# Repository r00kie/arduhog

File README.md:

# Arduhog #

The aim of this project is to create pcb diagrams and software thanks to it will be possible to build hardware cockpit simulator for DCS A10C (and maybe more). PCB board and software try to simulate HID interface (keyboard exactly), so the knowledge that it is available here should also fit for other simulators/games. 

I'm lazy so im using Arduino Nano as main controller, it's cheap (if you are using chinese replacements), it's popular, you don't need any advanced hardware programmer and when you will be bored with this project you can use it for something else.

Project requires [this library](https://git.io/vgGM2) for working. You have to install it in your Arduino IDE.

You can also check [DCS-Bios](http://dcs-bios.a10c.de/), but it have a different approach, it's requires installing some additional scripts in DCS World and it's works only with A10C Cocpit. 

## Project Structure Description

### Hardware ###

  * eagle/ - directory containing EAGLE project; 
  * eagle/main_board - pcb diagrams for main board; mainly it contains all necessary components to simulate hardware keyboard and other stuff to indicate device status, some buttons (currently they do nothing); main board have 8 expansions port for extension board, it allows you to, theoretically, support up to 64 buttons/switches; connection to the PC is done via the USB B port (why B? because it is the simplest USB port for soldering and it fit to 100 mil boards)
  * eagle/ext_board - pcb diagrams for extension board; thanks to this board you can connect up to 16 button; 
  * eagle/ahcp - only schematic, how to connect switches from Armament Hud Control Panel to port what will fit extension board;
  * eagle/bom/* - Bill of Materials for pcb boards;
  * eagle/tests/* - tests and early material created for this project;

### Software ###

  * src/arduhog/* - source code for arduino controller;
  * src/arduhog/keymappings.ods - spreedsheet containing mapping from eagle/ahcp.sch to buttons in code and shortcuts in game.  

## Screenshots, images and movies  
  
  * [Image gallery of prototype](https://imgur.com/a/71ZCE)
  * [Working prototype](https://vid.me/YhLZ)

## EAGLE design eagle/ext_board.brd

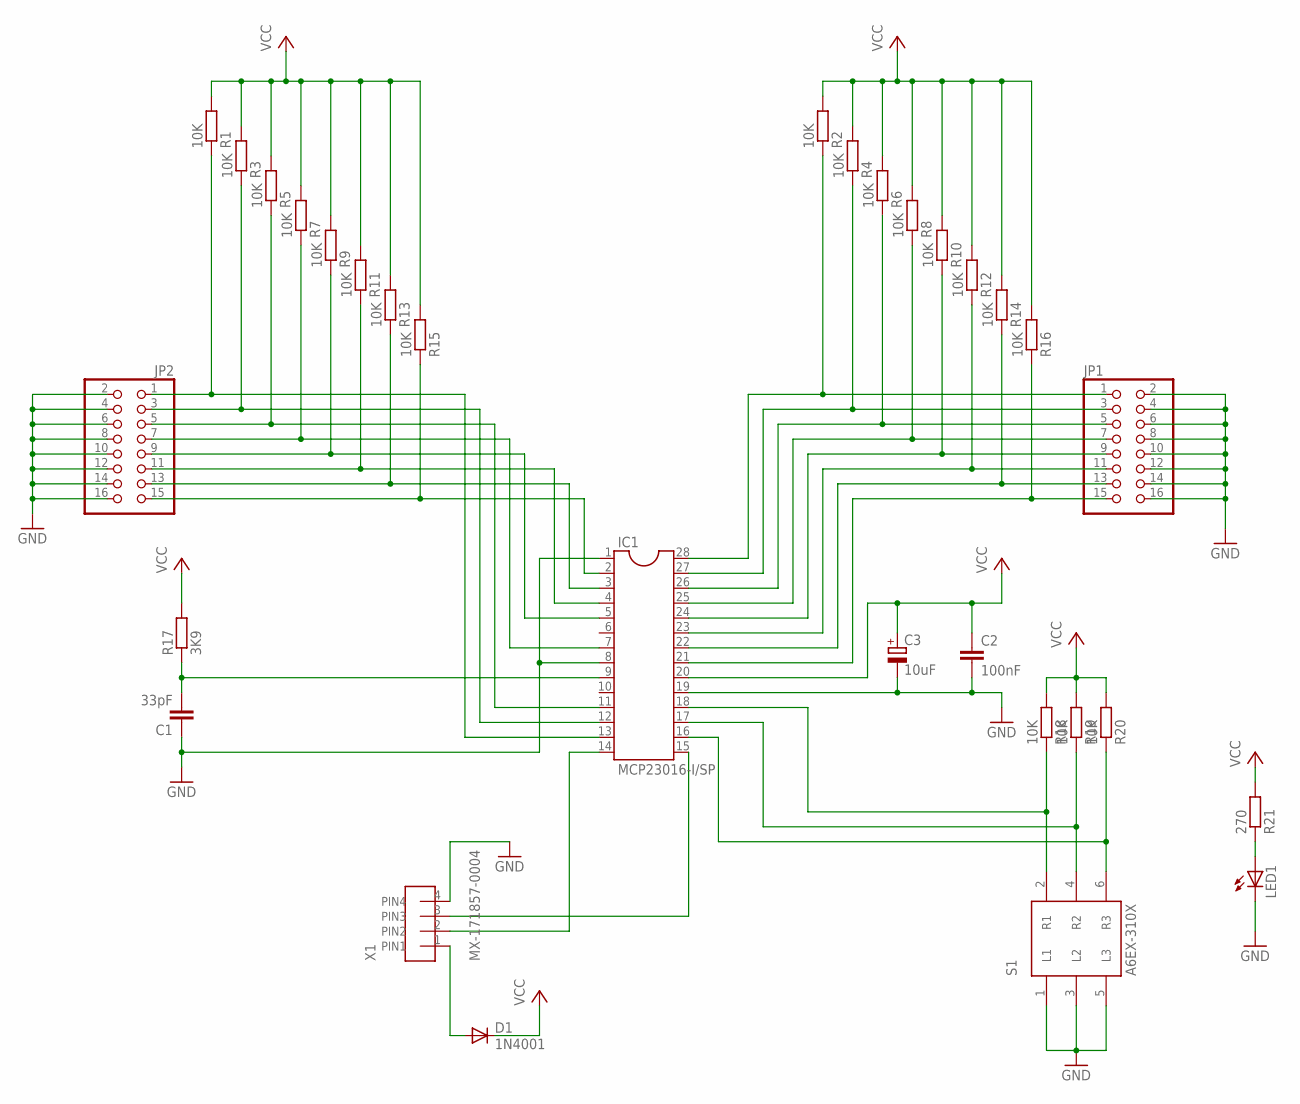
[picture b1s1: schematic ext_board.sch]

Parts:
C1: 33pF; C050-030X075
C2: 100nF; C050-030X075
C3: 10uF; E2,5-7
D1: 1N4001; DO41-10
IC1: MCP23016-I/SP; DIL28-3
JP1, JP2: PINHD-2X8; 2X08
LED1: LED3MM
R1, R2, R3, R4, R5, R6, R7, R8, R9, R10, R11, R12, R13, R14, R15, R16, R18, R19, R20: 10K; 0204/7
R17: 3K9; 0204/7
R21: 270; 0204/7
S1: A6EX-310X
X1: MX-171857-0004

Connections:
GND: C1.1, C2.2, C3.-, IC1.1, IC1.8, IC1.19, JP1.2, JP1.4, JP1.6, JP1.8, JP1.10, JP1.12, JP1.14, JP1.16, JP2.2, JP2.4, JP2.6, JP2.8, JP2.10, JP2.12, JP2.14, JP2.16, LED1.K (C), S1.1 (L1), S1.3 (L2), S1.5 (L3), X1.4 (PIN4)
GP0.0: IC1.21, JP1.15, R16.1
GP0.1: IC1.22, JP1.13, R14.1
GP0.2: IC1.23, JP1.11, R12.1
GP0.3: IC1.2, JP2.15, R15.1
GP0.4: IC1.3, JP2.13, R13.1
GP0.5: IC1.4, JP2.11, R11.1
unnamed: C1.2, IC1.9, R17.1
unnamed: IC1.18, R18.1, S1.2 (R1)
unnamed: IC1.17, R19.1, S1.4 (R2)
unnamed: IC1.5, JP2.9, R9.1
unnamed: IC1.7, JP2.7, R7.1
unnamed: D1.A, X1.1 (PIN1)
unnamed: IC1.11, JP2.5, R5.1
unnamed: IC1.16, R20.1, S1.6 (R3)
unnamed: IC1.24, JP1.9, R10.1
unnamed: IC1.25, JP1.7, R8.1
unnamed: IC1.26, JP1.5, R6.1
unnamed: IC1.27, JP1.3, R4.1
unnamed: IC1.28, JP1.1, R2.1
unnamed: IC1.12, JP2.3, R3.1
unnamed: IC1.13, JP2.1, R1.1
unnamed: LED1.A, R21.1
SCL: IC1.14, X1.2 (PIN2)
SDA: IC1.15, X1.3 (PIN3)
VCC: C2.1, C3.+, D1.C, IC1.20, R1.2, R2.2, R3.2, R4.2, R5.2, R6.2, R7.2, R8.2, R9.2, R10.2, R11.2, R12.2, R13.2, R14.2, R15.2, R16.2, R17.2, R18.2, R19.2, R20.2, R21.2

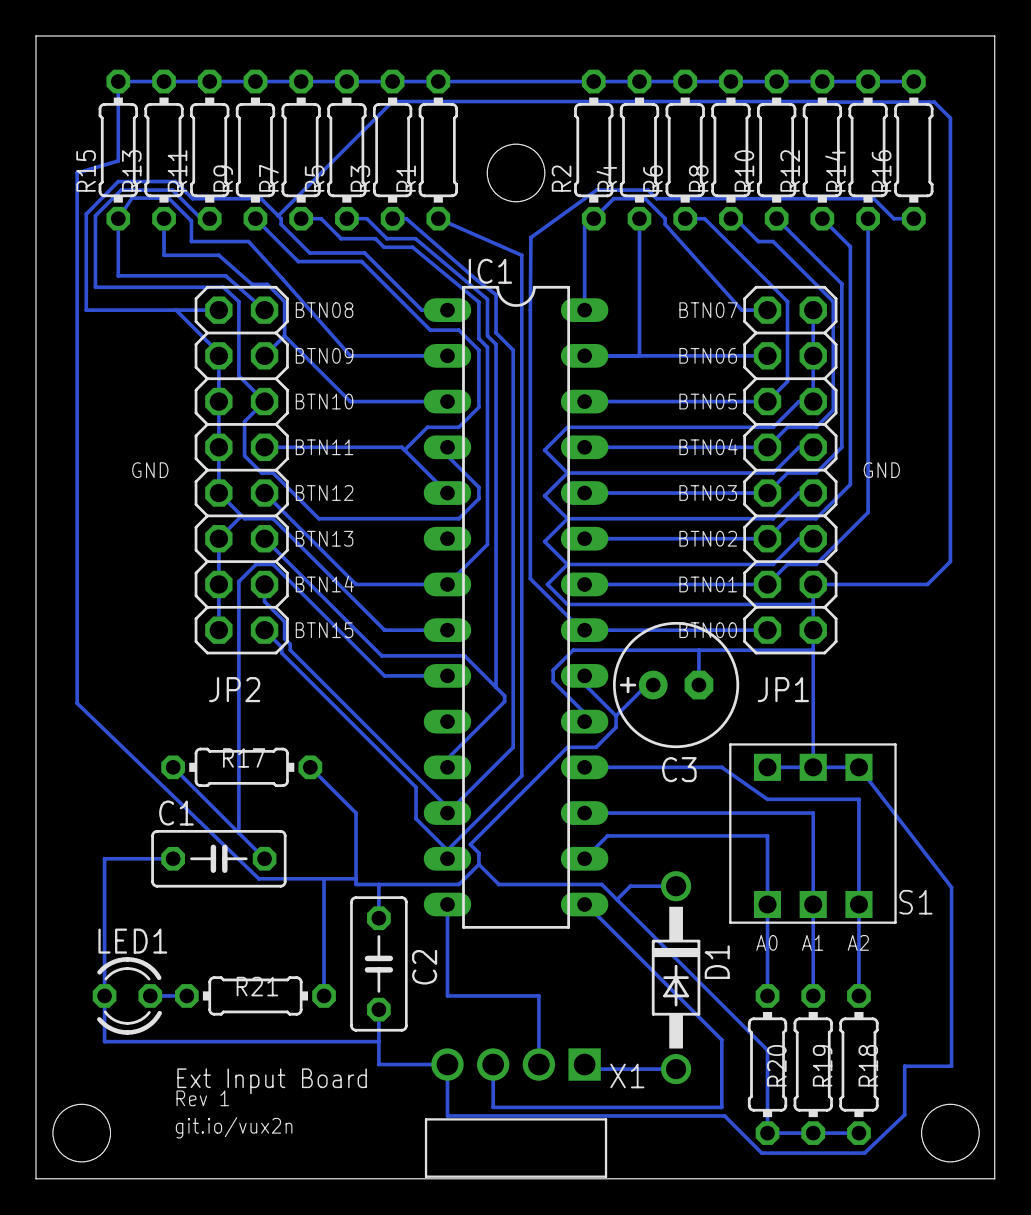
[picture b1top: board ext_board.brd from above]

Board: 2 copper layers, 53.3 x 63.5 mm, 31 parts (0 on the bottom side), 26 nets.

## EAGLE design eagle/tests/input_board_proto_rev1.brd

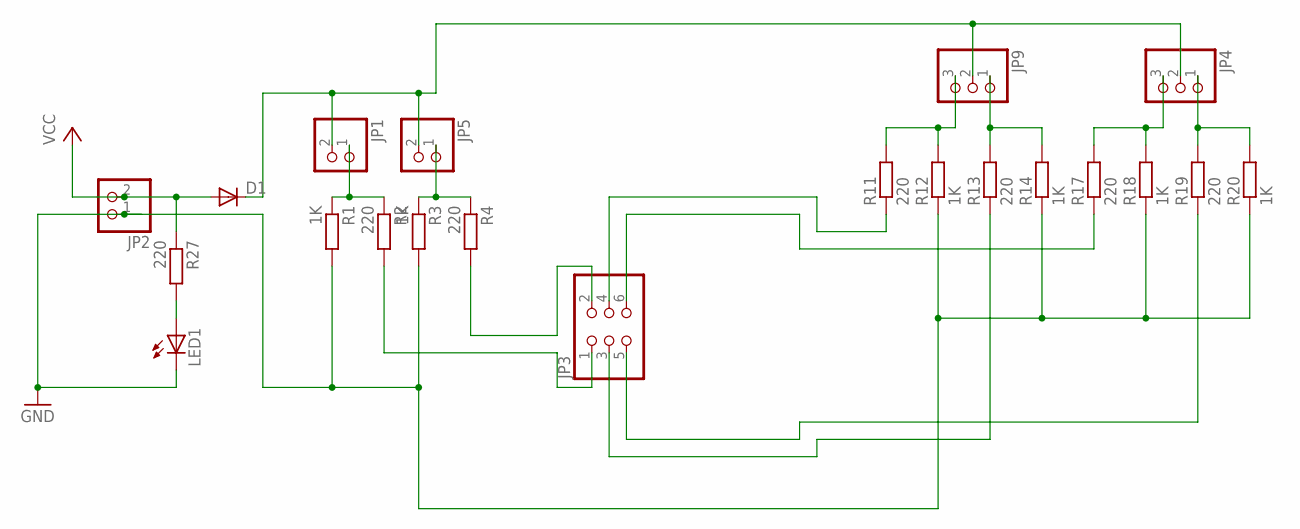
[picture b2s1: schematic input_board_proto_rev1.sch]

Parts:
D1: DIODE-C1702-05; C1702-05
JP1, JP2, JP5: PINHD-1X2; 1X02
JP3: PINHD-2X3; 2X03
JP4, JP9: PINHD-1X3; 1X03
LED1: LED3MM
R1, R3, R12, R14, R18, R20: 1K; 0204V
R2, R4, R11, R13, R17, R19, R27: 220; 0204V

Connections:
GND: JP2.1, LED1.K (C), R1.2, R3.2, R12.1, R14.1, R18.1, R20.1
unnamed: JP1.1, R1.1, R2.1
unnamed: JP5.1, R3.1, R4.1
unnamed: JP3.1, R2.2
unnamed: JP3.2, R4.2
unnamed: JP9.3, R11.2, R12.2
unnamed: JP9.1, R13.2, R14.2
unnamed: JP4.3, R17.2, R18.2
unnamed: JP4.1, R19.2, R20.2
unnamed: JP3.6, R17.1
unnamed: JP3.4, R11.1
unnamed: JP3.5, R19.1
unnamed: JP3.3, R13.1
unnamed: LED1.A, R27.2
unnamed: D1.C, JP1.2, JP4.2, JP5.2, JP9.2
VCC: D1.A, JP2.2, R27.1

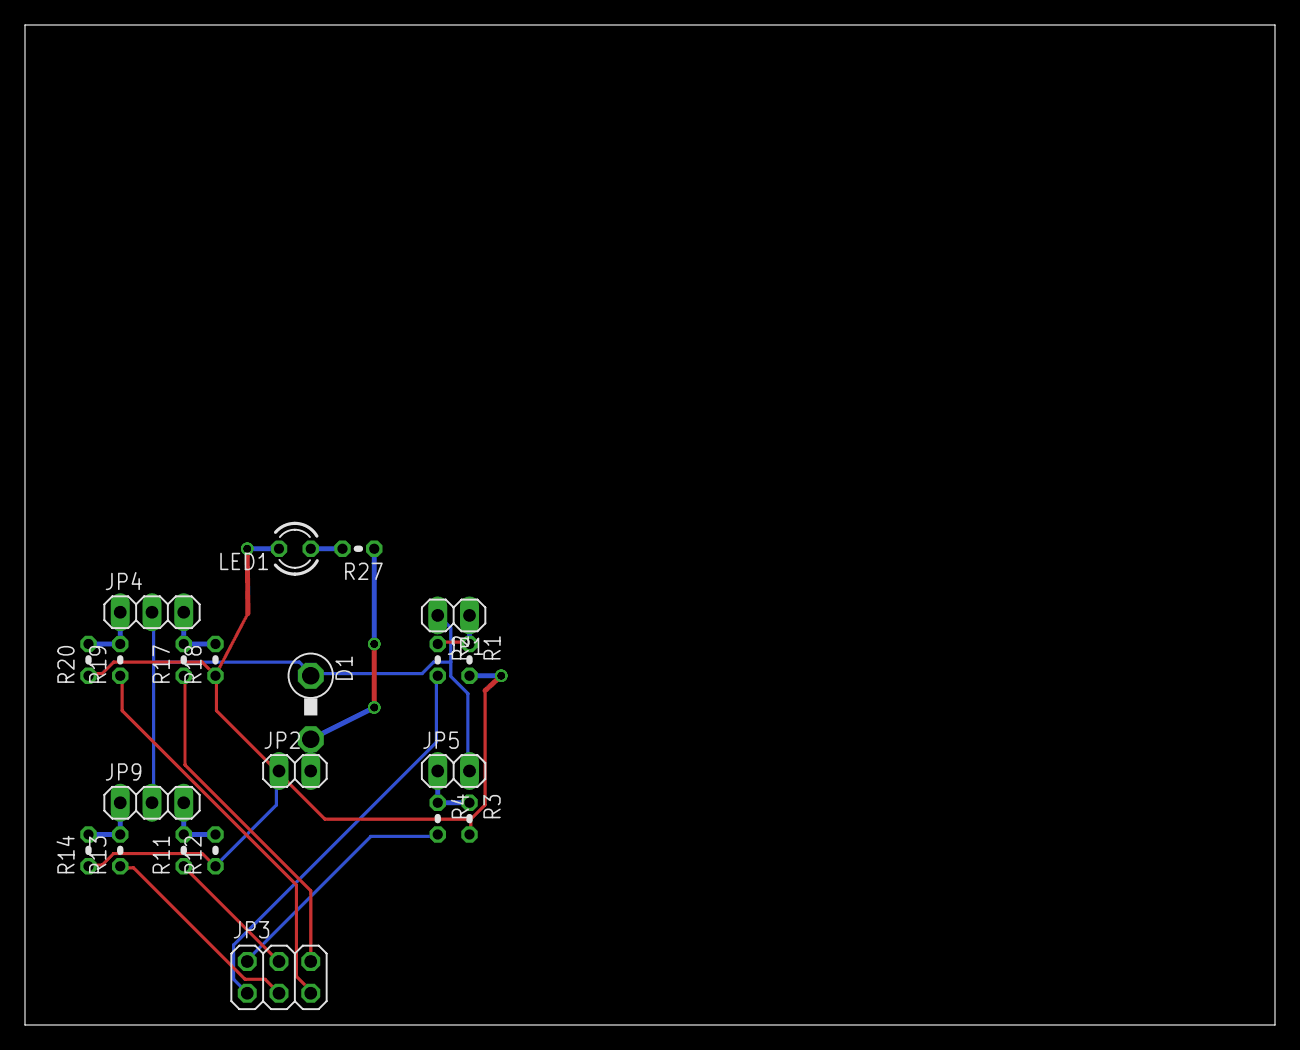
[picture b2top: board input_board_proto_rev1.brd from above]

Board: 2 copper layers, 100.0 x 80.0 mm, 21 parts (0 on the bottom side), 16 nets.

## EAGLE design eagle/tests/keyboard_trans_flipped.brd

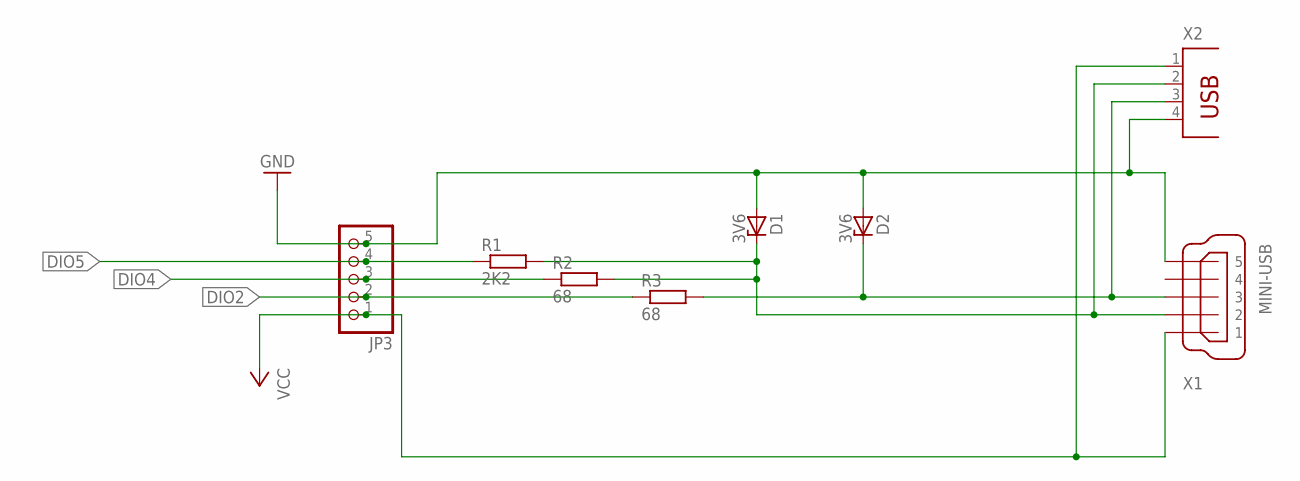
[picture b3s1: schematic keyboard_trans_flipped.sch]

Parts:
D1, D2: 3V6; DO35Z10
JP3: PINHD-1X5; 1X05
R1: 2K2; 0204/5
R2, R3: 68; 0204/5
X1: MINI-USB; UX60-MB-5S8
X2: PN61729

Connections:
DIO2: JP3.2, R3.1
DIO4: JP3.3, R2.1
DIO5: JP3.4, R1.1
GND: D1.A, D2.A, JP3.5, X1.5, X2.4
unnamed: D1.C, R1.2, R2.2, X1.2, X2.2
unnamed: D2.C, R3.2, X1.3, X2.3
VCC: JP3.1, X1.1, X2.1

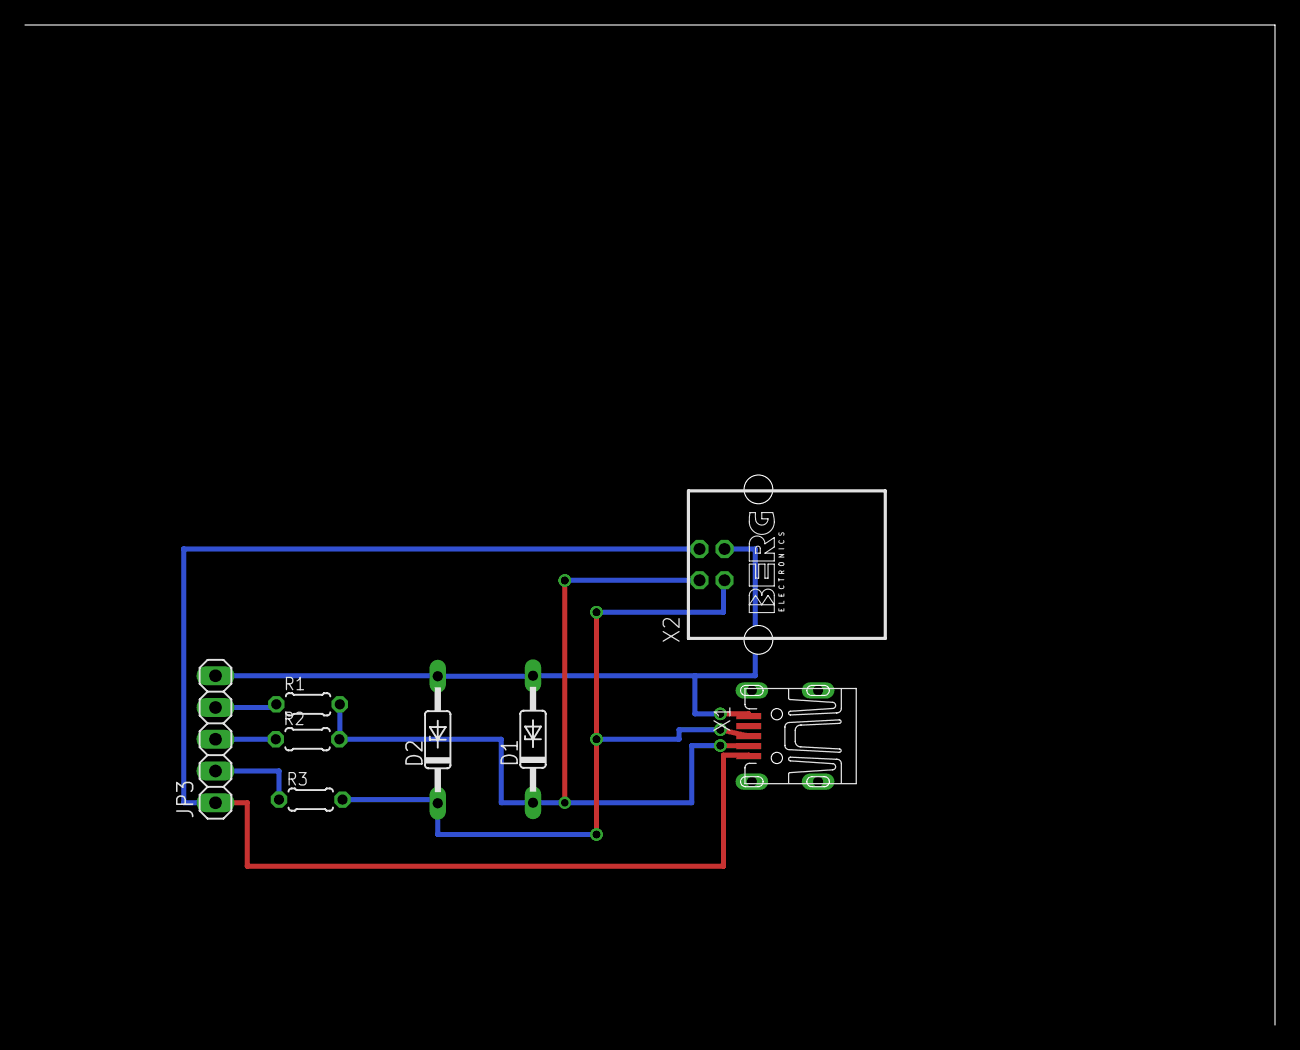
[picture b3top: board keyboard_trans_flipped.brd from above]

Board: 2 copper layers, 100.0 x 80.0 mm, 8 parts (0 on the bottom side), 7 nets.

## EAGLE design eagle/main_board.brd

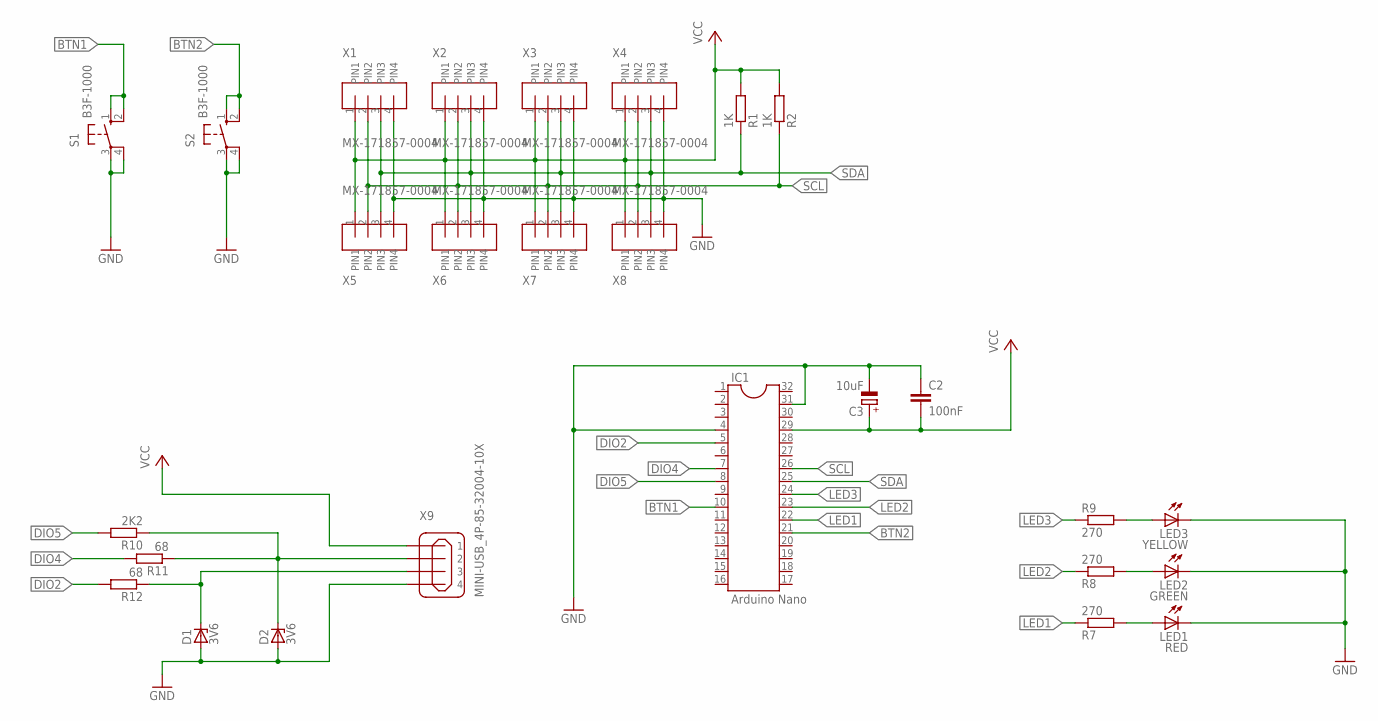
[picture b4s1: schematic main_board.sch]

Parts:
C2: 100nF; C050-030X075
C3: 10uF; E2,5-7
D1, D2: 3V6; DO35Z10
IC1: Arduino Nano; DIL32
LED1: RED; LED3MM
LED2: GREEN; LED3MM
LED3: YELLOW; LED3MM
R1, R2: 1K; 0204/7
R7, R8, R9: 270; 0204/7
R10: 2K2; 0204/7
R11, R12: 68; 0204/7
S1, S2: B3F-1000; B3F-10XX
X1, X2, X3, X4, X5, X6, X7, X8: MX-171857-0004
X9: MINI-USB_4P-85-32004-10X; 85-32004-10X

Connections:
BTN1: IC1.10, S1.1 (S), S1.2 (S1)
BTN2: IC1.21, S2.1 (S), S2.2 (S1)
DIO2: IC1.5, R12.2
DIO4: IC1.7, R11.2
DIO5: IC1.8, R10.2
GND: C2.1, C3.-, D1.A, D2.A, IC1.4, IC1.31, LED1.K (C), LED2.K (C), LED3.K (C), S1.3, S1.4 (P1), S2.3, S2.4 (P1), X1.4 (PIN4), X2.4 (PIN4), X3.4 (PIN4), X4.4 (PIN4), X5.4 (PIN4), X6.4 (PIN4), X7.4 (PIN4), X8.4 (PIN4), X9.4
LED1: IC1.22, R7.1
LED2: IC1.23, R8.1
LED3: IC1.24, R9.1
unnamed: LED3.A, R9.2
unnamed: D1.C, R12.1, X9.3
unnamed: D2.C, R10.1, R11.1, X9.2
unnamed: LED2.A, R8.2
unnamed: LED1.A, R7.2
SCL: IC1.26, R2.1, X1.2 (PIN2), X2.2 (PIN2), X3.2 (PIN2), X4.2 (PIN2), X5.2 (PIN2), X6.2 (PIN2), X7.2 (PIN2), X8.2 (PIN2)
SDA: IC1.25, R1.1, X1.3 (PIN3), X2.3 (PIN3), X3.3 (PIN3), X4.3 (PIN3), X5.3 (PIN3), X6.3 (PIN3), X7.3 (PIN3), X8.3 (PIN3)
VCC: C2.2, C3.+, IC1.29, R1.2, R2.2, X1.1 (PIN1), X2.1 (PIN1), X3.1 (PIN1), X4.1 (PIN1), X5.1 (PIN1), X6.1 (PIN1), X7.1 (PIN1), X8.1 (PIN1), X9.1

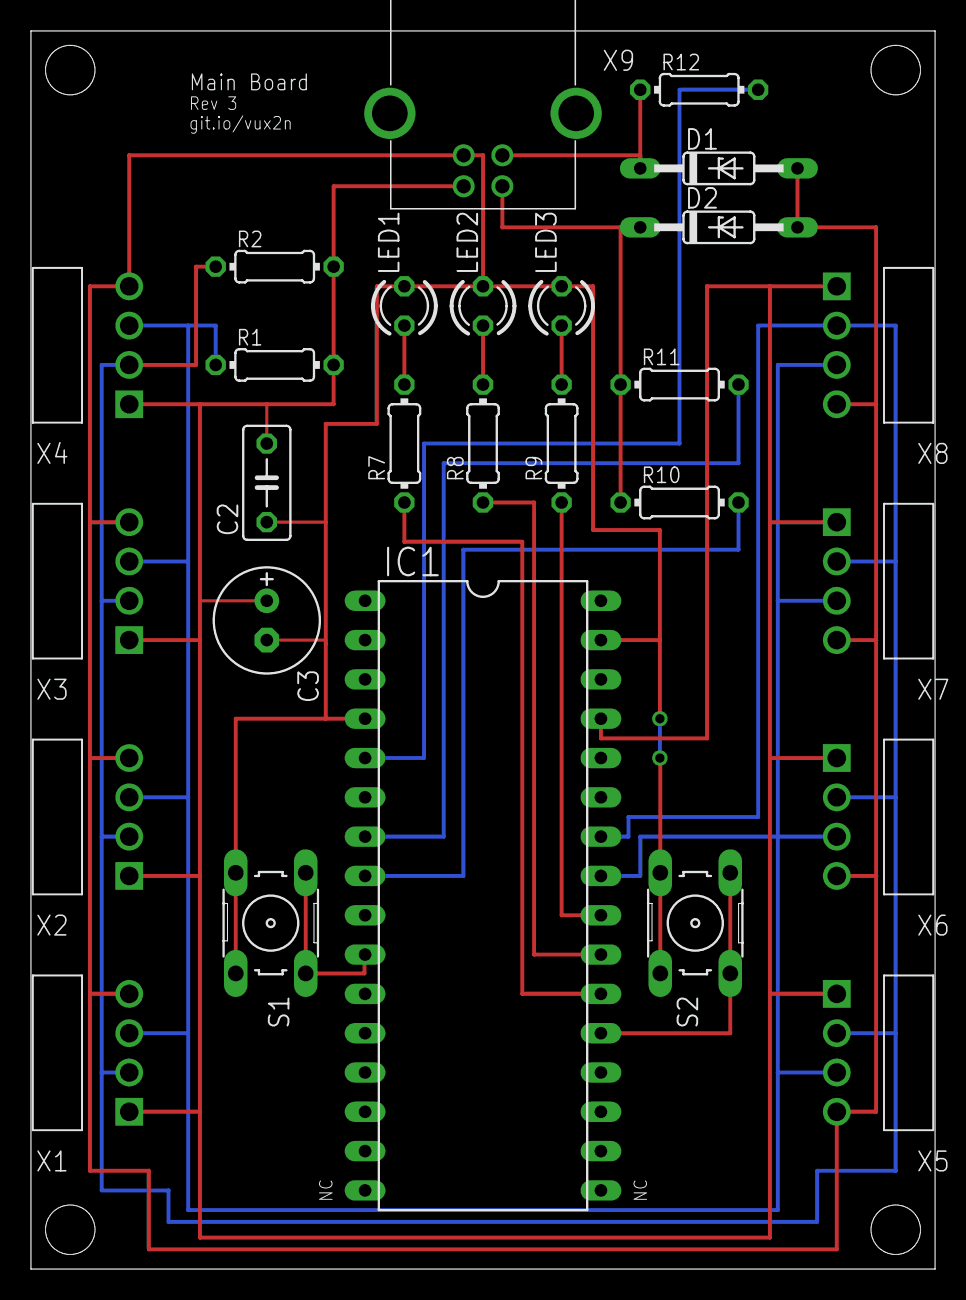
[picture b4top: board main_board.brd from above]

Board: 2 copper layers, 58.4 x 80.0 mm, 27 parts (0 on the bottom side), 17 nets.

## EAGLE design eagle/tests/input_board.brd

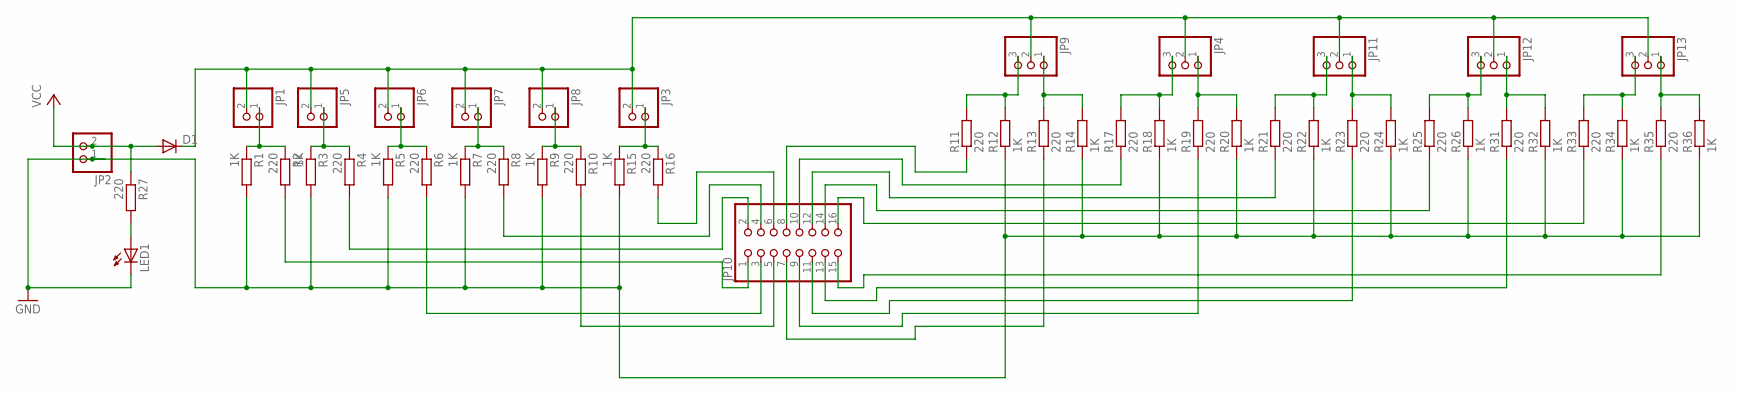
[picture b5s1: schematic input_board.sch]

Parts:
D1: DIODE-C1702-05; C1702-05
JP1, JP2, JP3, JP5, JP6, JP7, JP8: PINHD-1X2; 1X02
JP4, JP9, JP11, JP12, JP13: PINHD-1X3; 1X03
JP10: PINHD-2X8; 2X08
LED1: LED3MM
R1, R3, R5, R7, R9, R12, R14, R15, R18, R20, R22, R24, R26, R32, R34, R36: 1K; 0204V
R2, R4, R6, R8, R10, R11, R13, R16, R17, R19, R21, R23, R25, R27, R31, R33, R35: 220; 0204V

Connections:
GND: JP2.1, LED1.K (C), R1.2, R3.2, R5.2, R7.2, R9.2, R12.1, R14.1, R15.2, R18.1, R20.1, R22.1, R24.1, R26.1, R32.1, R34.1, R36.1
unnamed: JP1.1, R1.1, R2.1
unnamed: JP3.1, R15.1, R16.1
unnamed: JP10.16, R33.1
unnamed: JP5.1, R3.1, R4.1
unnamed: JP6.1, R5.1, R6.1
unnamed: JP7.1, R7.1, R8.1
unnamed: JP8.1, R9.1, R10.1
unnamed: JP10.1, R2.2
unnamed: JP10.2, R4.2
unnamed: JP10.3, R6.2
unnamed: JP10.4, R8.2
unnamed: JP10.5, R10.2
unnamed: JP10.6, R16.2
unnamed: JP9.3, R11.2, R12.2
unnamed: JP9.1, R13.2, R14.2
unnamed: JP10.14, R25.1
unnamed: JP4.3, R17.2, R18.2
unnamed: JP4.1, R19.2, R20.2
unnamed: JP11.3, R21.2, R22.2
unnamed: JP11.1, R23.2, R24.2
unnamed: JP12.3, R25.2, R26.2
unnamed: JP12.1, R31.2, R32.2
unnamed: JP13.3, R33.2, R34.2
unnamed: JP13.1, R35.2, R36.2
unnamed: JP10.12, R21.1
unnamed: JP10.10, R17.1
unnamed: JP10.8, R11.1
unnamed: JP10.15, R35.1
unnamed: JP10.13, R31.1
unnamed: JP10.11, R23.1
unnamed: JP10.9, R19.1
unnamed: JP10.7, R13.1
unnamed: LED1.A, R27.2
unnamed: D1.C, JP1.2, JP3.2, JP4.2, JP5.2, JP6.2, JP7.2, JP8.2, JP9.2, JP11.2, JP12.2, JP13.2
VCC: D1.A, JP2.2, R27.1

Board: 2 copper layers, 48 parts (0 on the bottom side), 36 nets, no tracks yet.

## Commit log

2016-02-07 Initial project commit
2016-02-07 fixed README formatting
